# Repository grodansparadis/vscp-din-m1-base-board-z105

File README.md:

# vscp-din-m1-base-board
Base board for all VSCP DIN M1 modules

**Note!** This is still a prototype.

## PCB's

---

Part of the [VSCP Project](https://www.vscp.org).

Copyright 2021-2026 © Åke Hedman, (Grodans Paradis AB)[https://www.grodansparadis.com]

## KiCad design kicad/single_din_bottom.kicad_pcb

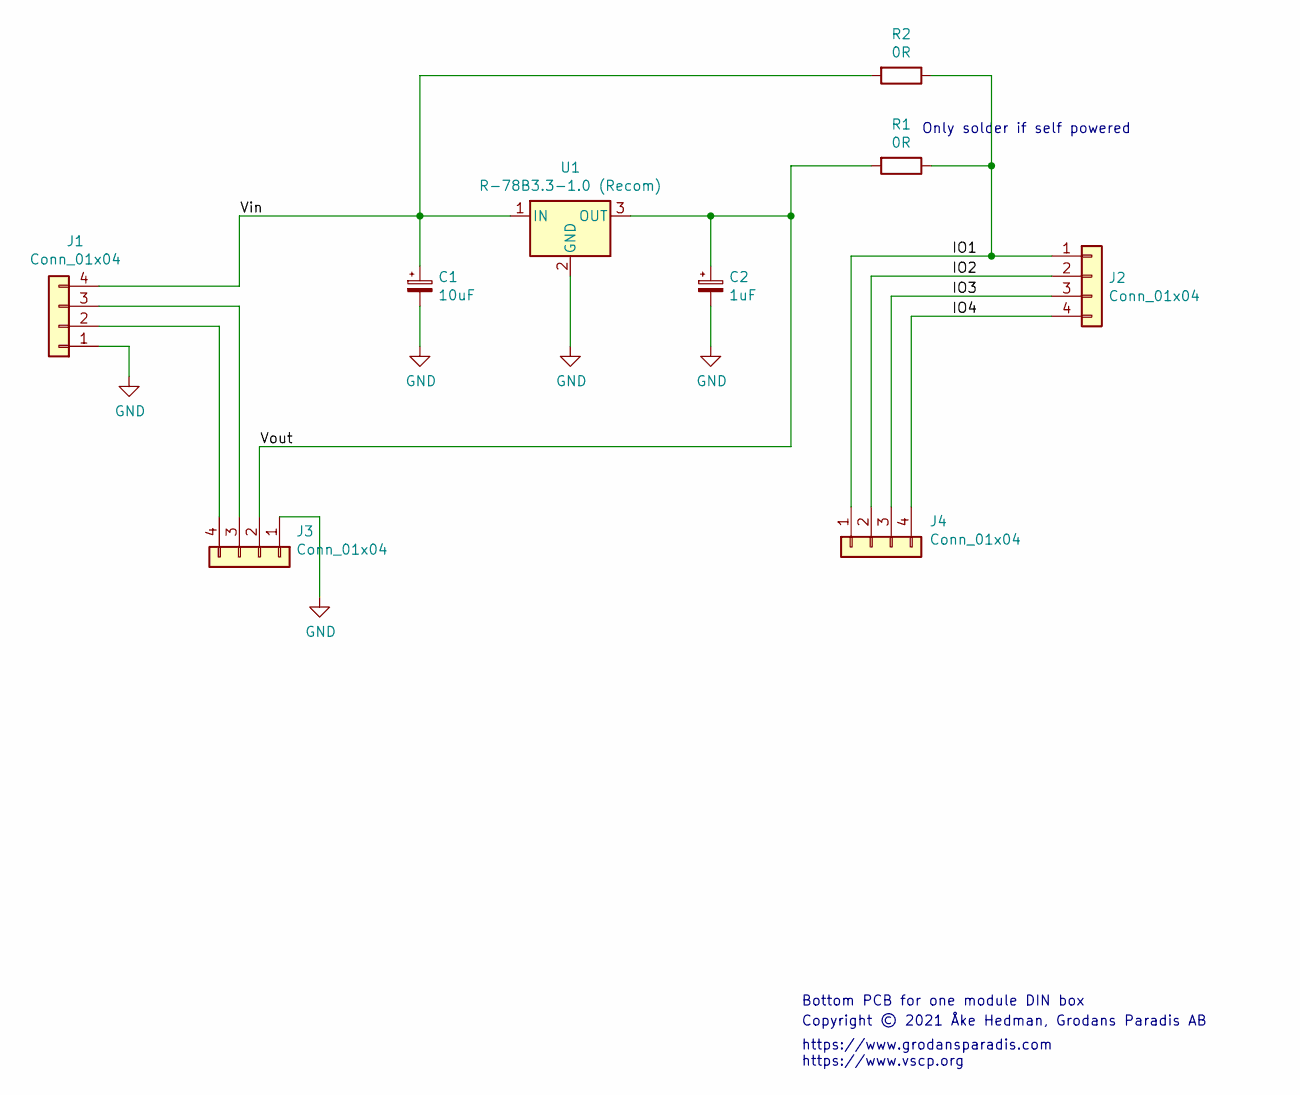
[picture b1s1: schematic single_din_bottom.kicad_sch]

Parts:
C1: 10uF; CP_Radial_D5.0mm_P2.50mm
C2: 1uF; CP_Radial_D5.0mm_P2.50mm
J1, J2: Conn_01x04; PinHeader_1x04_P2.54mm_Horizontal
J3, J4: Conn_01x04; PinHeader_1x04_P2.54mm_Vertical
R1, R2: 0R; R_0805_2012Metric
U1: R-78B3.3-1.0 (Recom); Converter_DCDC_RECOM_R-78B-2.0_THT

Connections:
/IO1: J2.1, J4.1, R1.1, R2.1
/IO2: J2.2, J4.2
/IO3: J2.3, J4.3
/IO4: J2.4, J4.4
/Vin: C1.1, J1.4, R2.2, U1.1 (IN)
/Vout: C2.1, J3.2, R1.2, U1.3 (OUT)
GND: C1.2, C2.2, J1.1, J3.1, U1.2 (GND)
unnamed: J1.2, J3.4
unnamed: J1.3, J3.3

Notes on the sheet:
Bottom PCB for one module DIN box
Copyright © 2021 Åke Hedman, Grodans Paradis AB
Only solder if self powered
https://www.grodansparadis.com https://www.vscp.org

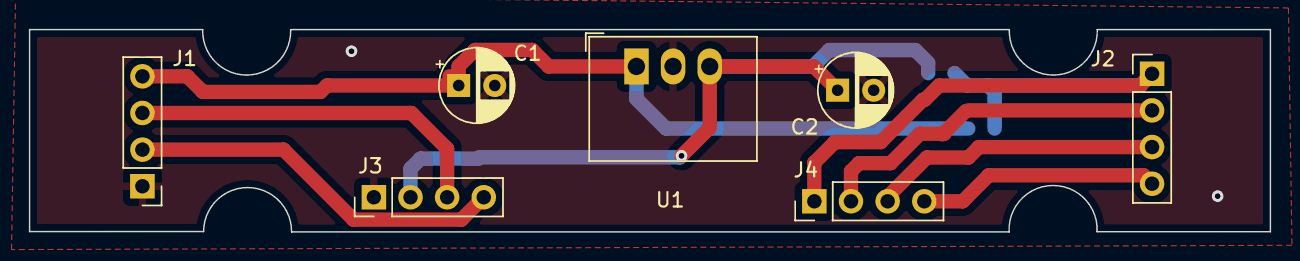
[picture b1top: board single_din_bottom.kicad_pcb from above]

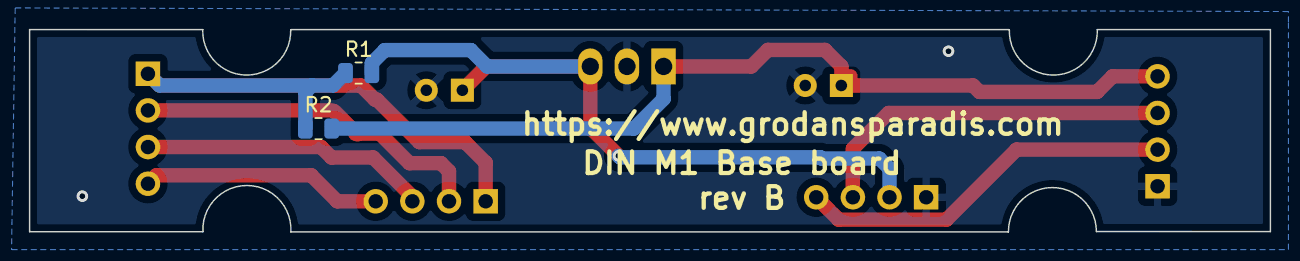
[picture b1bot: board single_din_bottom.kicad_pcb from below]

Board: 2 copper layers, 86.0 x 14.0 mm, 9 parts (2 on the bottom side), 9 nets.

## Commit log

2021-05-20 Initital checkin
2021-05-20 Added rev
2021-05-20 Added self power possibilities
2021-05-21 Added gerbers
2021-05-24 Added measurements to drawing
2021-05-24 Fixed front silc
2021-05-25 Fixed board to board connectors
2021-05-25 Adding gerbers
2021-05-25 Added info
2021-08-09 Added cutots
2021-08-10 Fixed ground plane
2021-08-10 Please enter the commit message for your changes. Lines starting
2022-06-15 Fixed som design errors
2022-09-02 Updated copyright
2025-06-05 Updated copyright year
